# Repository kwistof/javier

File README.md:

<p align="center">
  <picture>
    <source media="(prefers-color-scheme: dark)" srcset="docs/images/logo-dark.svg">
    
  </picture>
</p>

Javier is a 36-key wireless split keyboard. It uses Kailh Choc v1 switches in hot-swap sockets, nice!nano v2 controllers and [ZMK](https://zmk.dev). Both hands use the same PCB and plate.

<p align="center">
  <picture>
    <source media="(prefers-color-scheme: dark)" srcset="docs/images/hero-dark.png">
    
  </picture>
</p>

## Features

- **Wireless.** Each half has its own nice!nano v2 and battery. The halves connect to each other and to the computer over Bluetooth, with no cables.
- **Hotswappable.** Every switch can sit in a Kailh Choc socket, so you can change switches without solder. The sockets are optional: you can also solder the switches directly to the PCB.
- **Diodeless.** Each key connects directly to its own controller pin, so there is no diode matrix. There are fewer parts to solder and fewer joints that can fail.
- **Reversible PCB.** The left and right halves use the same PCB and the same plate. You order one design and turn it over for the other hand.

## Build

<p align="center">
  
  &nbsp;&nbsp;&nbsp;
  
  &nbsp;&nbsp;&nbsp;
  
</p>

<p align="center"><em>Case, PCB and plate</em></p>

Follow the [build guide](docs/build-guide.md).

## Firmware

The firmware builds with GitHub Actions on every push. The included keymap is a plain QWERTY starting point.

1. Fork this repository and enable Actions.
2. Edit [`javier.keymap`](config/boards/shields/javier/javier.keymap) and push.
3. Download the `firmware` artifact from the workflow run.

To learn how it works, see the [ZMK documentation](https://zmk.dev/docs) and its [keymap guide](https://zmk.dev/docs/keymaps).

## Files

| Path | Contents |
|------|----------|
| `hardware/production/` | Gerber files for the PCB and plate |
| `hardware/case/` | Printable left and right cases |
| `hardware/pcb/`, `hardware/plate/` | KiCad projects |
| [`docs/schematic.pdf`](docs/schematic.pdf) | Schematic |
| `config/` | ZMK configuration |

## Credits

Javier is inspired by these open-source keyboards:

- [Corne](https://github.com/foostan/crkbd) by foostan
- [Cantor](https://github.com/diepala/cantor) by Diego Palacios

## License

Firmware configuration: [MIT](LICENSE). Hardware: [CC BY-SA 4.0](hardware/LICENSE). See [third-party notices](THIRD_PARTY.md).

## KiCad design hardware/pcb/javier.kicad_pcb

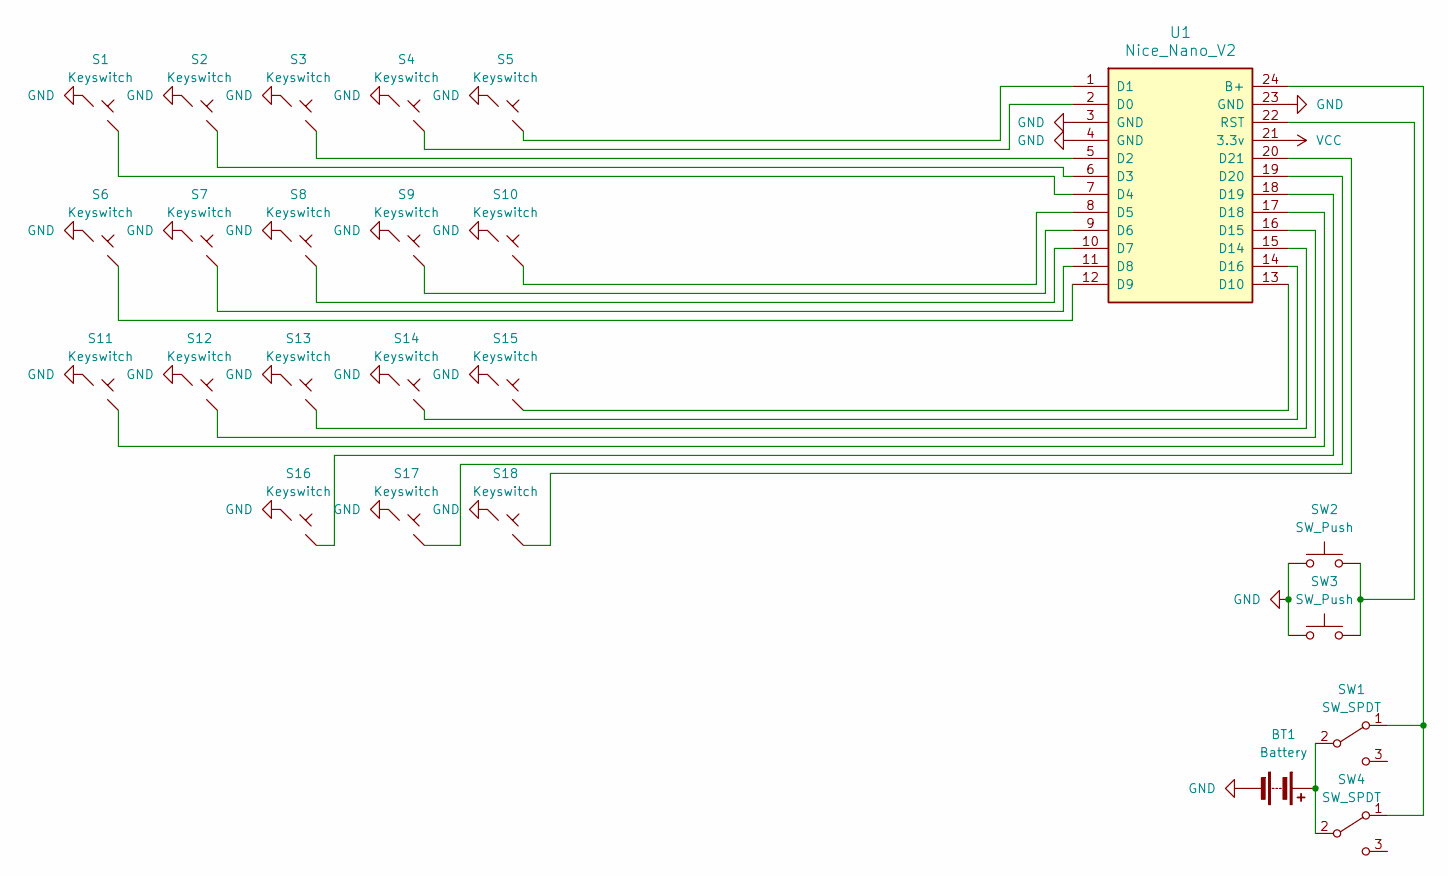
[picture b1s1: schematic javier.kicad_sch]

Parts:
BT1: Battery; Battery_Pads
S1, S2, S3, S4, S5, S6, S7, S8, S9, S10, S11, S12, S13, S14, S15, S16, S17, S18: Keyswitch; Kailh_socket_PG1350_optional_reversible
SW1, SW4: SW_SPDT; SW_SPDT_PCM12
SW2, SW3: SW_Push; SW_SPST_B3U-1000P
U1: Nice_Nano_V2; ProMicro_Reversible

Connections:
GND: BT1.2 (-), S1.1, S2.1, S3.1, S4.1, S5.1, S6.1, S7.1, S8.1, S9.1, S10.1, S11.1, S12.1, S13.1, S14.1, S15.1, S16.1, S17.1, S18.1, SW2.1, SW3.1, U1.3 (GND), U1.4 (GND), U1.23 (GND)
unnamed: BT1.1 (+), SW1.2 (B), SW4.2 (B)
unnamed: SW1.1 (A), SW4.1 (A), U1.24 (B+)
unnamed: S4.2, U1.2 (D0)
unnamed: S5.2, U1.1 (D1)
unnamed: S3.2, U1.5 (D2)
unnamed: S2.2, U1.6 (D3)
unnamed: S1.2, U1.7 (D4)
unnamed: S10.2, U1.8 (D5)
unnamed: S9.2, U1.9 (D6)
unnamed: S8.2, U1.10 (D7)
unnamed: S7.2, U1.11 (D8)
unnamed: S6.2, U1.12 (D9)
unnamed: S15.2, U1.13 (D10)
unnamed: S13.2, U1.15 (D14)
unnamed: S12.2, U1.16 (D15)
unnamed: S14.2, U1.14 (D16)
unnamed: S11.2, U1.17 (D18)
unnamed: S16.2, U1.18 (D19)
unnamed: S17.2, U1.19 (D20)
unnamed: S18.2, U1.20 (D21)
unnamed: SW2.2, SW3.2, U1.22 (RST)
VCC: U1.21 (3.3v)

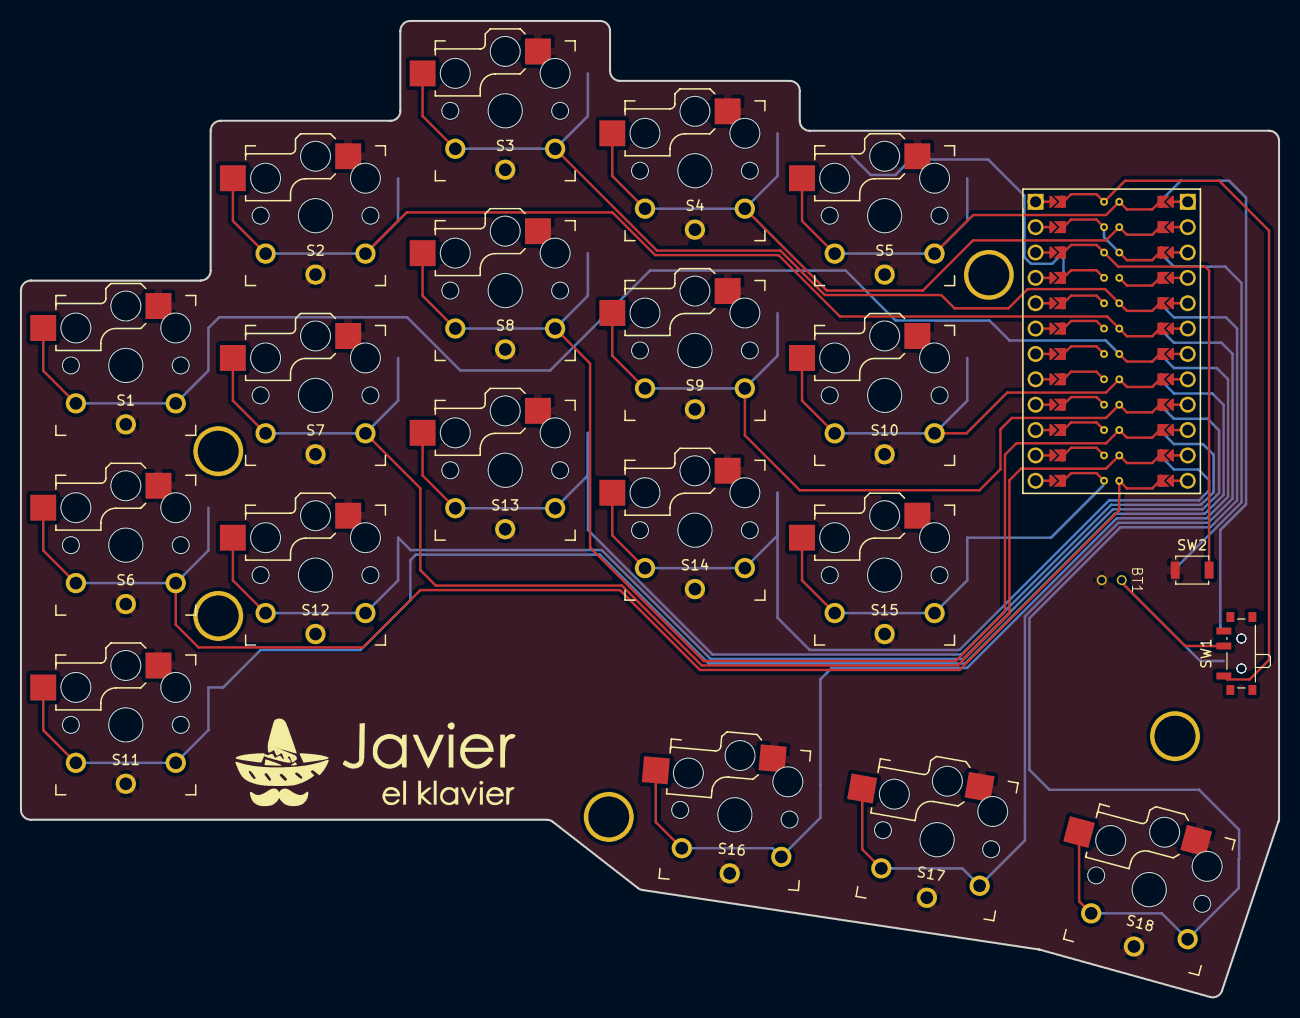
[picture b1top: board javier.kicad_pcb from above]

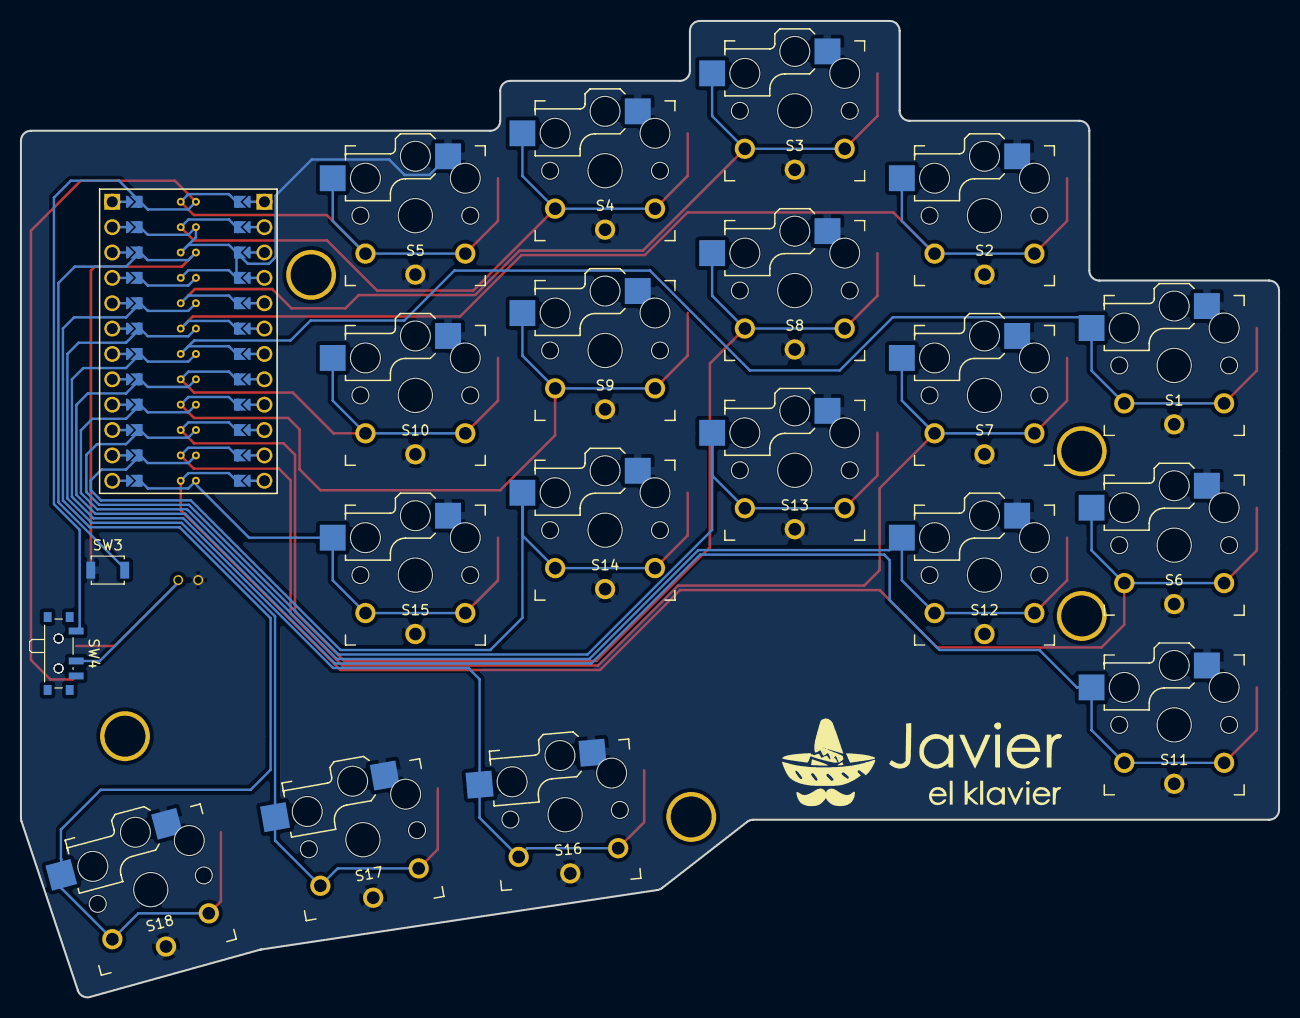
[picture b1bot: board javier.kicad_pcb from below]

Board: 2 copper layers, 126.0 x 97.8 mm, 24 parts (2 on the bottom side), 22 nets.
